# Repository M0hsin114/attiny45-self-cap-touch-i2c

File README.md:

# attiny45-self-cap-touch-i2c
A pocket-sized, 3.3 V capacitive-touch sensor board built around the ATtiny45/85.  
Four independent touch pads (PB1/PB3/PB4/PB5) wake on finger proximity and report touch events to a host (Raspberry Pi, Arduino, ESP32 …) over standard I²C.  
Hardware is open-source: KiCad 9 project with 1-layer PCB, 15.5mm×16mm, easy to hand-solder.

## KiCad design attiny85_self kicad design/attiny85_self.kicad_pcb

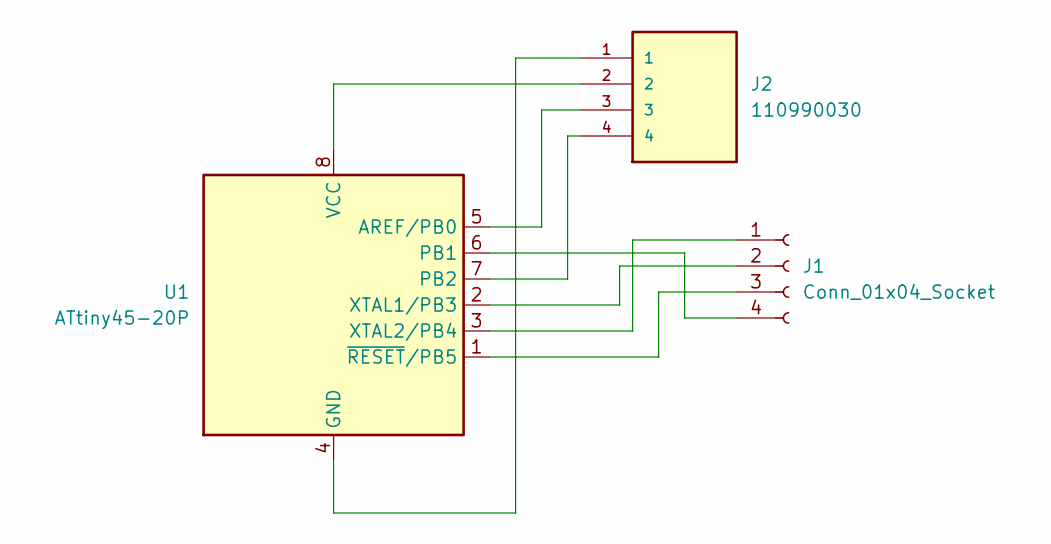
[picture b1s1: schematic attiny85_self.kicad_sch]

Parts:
J1: Conn_01x04_Socket; PinSocket_1x04_P1.00mm_Vertical
J2: 110990030; SEEED_110990030; PARTREV A
U1: ATtiny45-20P; DIP-8_W7.62mm

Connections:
unnamed: J1.1, U1.3 (XTAL2/PB4)
unnamed: J1.2, U1.2 (XTAL1/PB3)
unnamed: J1.3, U1.1 (~RESET/PB5)
unnamed: J1.4, U1.6 (PB1)
unnamed: J2.3, U1.5 (AREF/PB0)
unnamed: J2.1, U1.4 (GND)
unnamed: J2.4, U1.7 (PB2)
unnamed: J2.2, U1.8 (VCC)

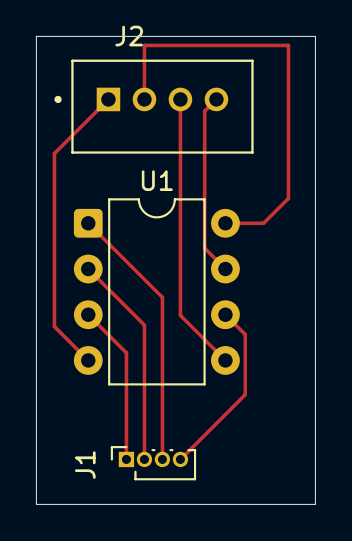
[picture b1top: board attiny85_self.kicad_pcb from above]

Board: 2 copper layers, 15.5 x 26.0 mm, 3 parts (0 on the bottom side), 8 nets.

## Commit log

2025-10-24 KiCad PCB + ATtiny cap-touch firmware
